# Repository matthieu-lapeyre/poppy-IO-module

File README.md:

poppy-IO-module
===============

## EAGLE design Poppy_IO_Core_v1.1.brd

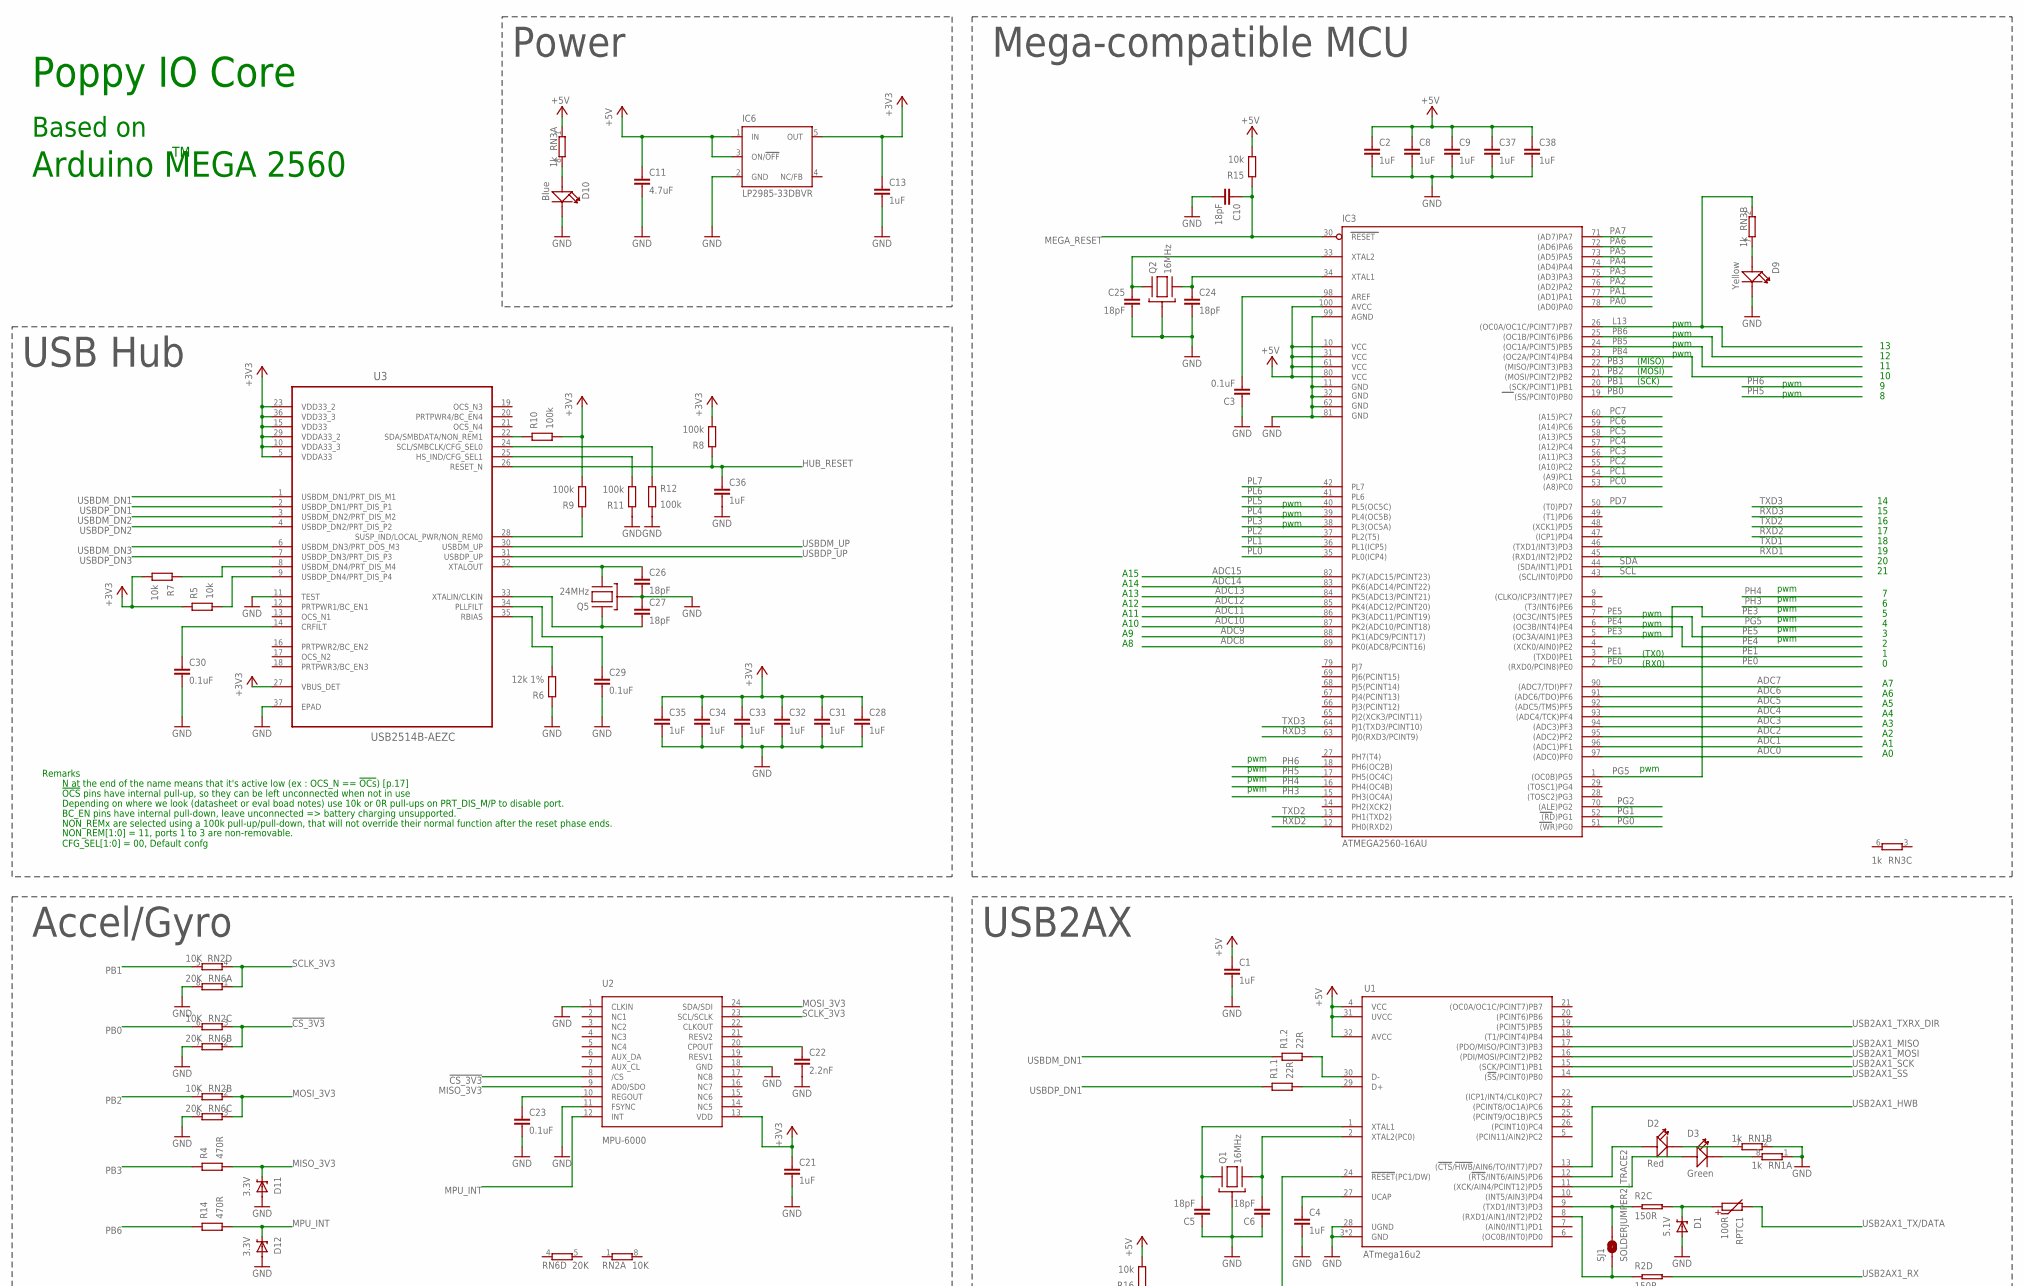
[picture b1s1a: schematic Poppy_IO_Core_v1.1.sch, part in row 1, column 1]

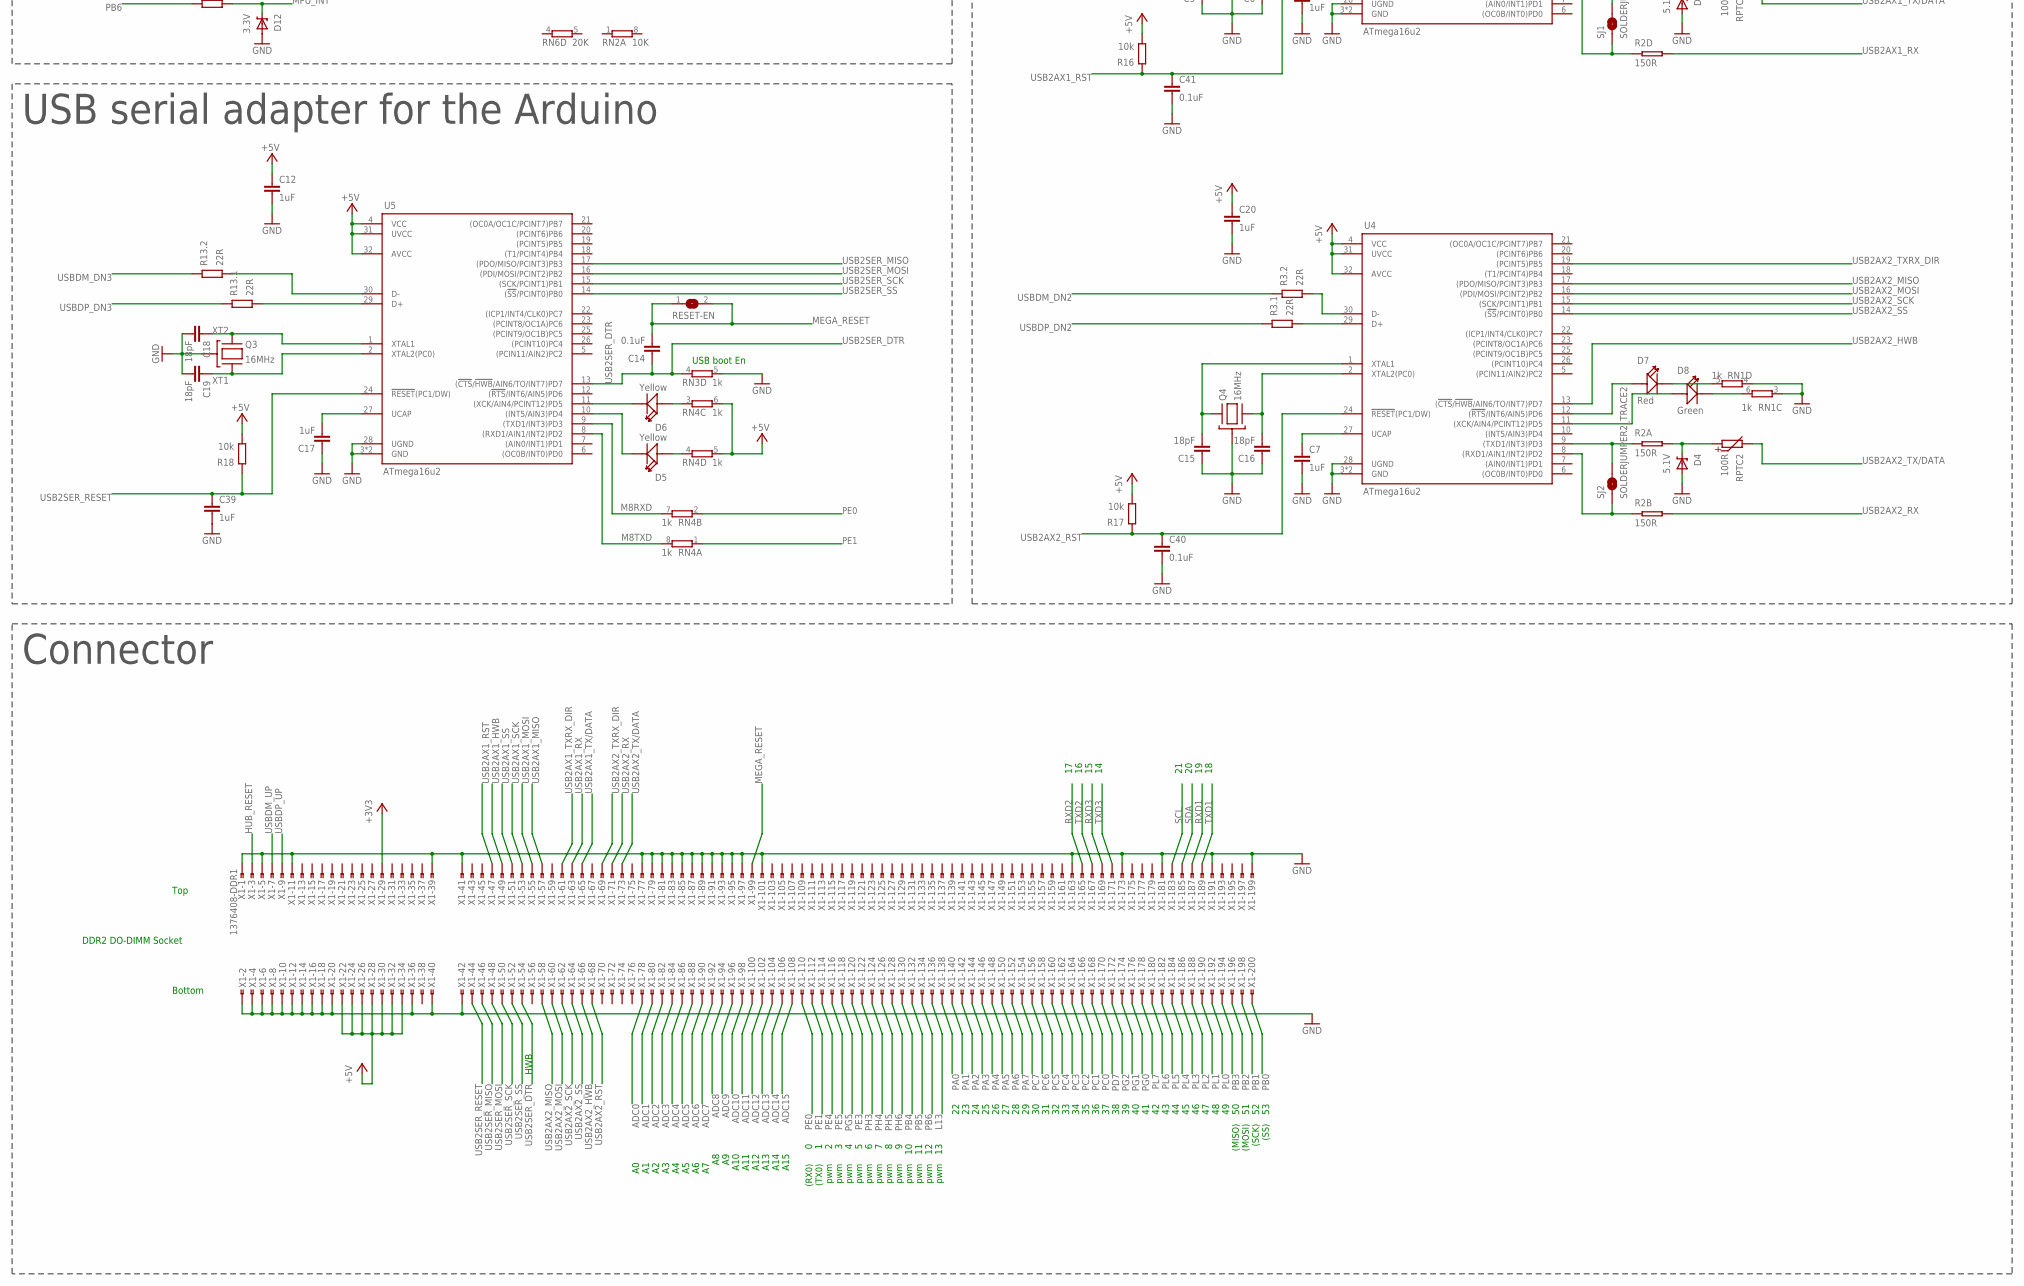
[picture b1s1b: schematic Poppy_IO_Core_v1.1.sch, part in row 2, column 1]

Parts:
C1, C2, C4, C7, C8, C9, C12, C13, C17, C20, C21, C28, C31, C32, C33, C34, C35, C36, C37, C38, C39: 1uF; 0402_N
C3, C14, C23, C29, C30, C40, C41: 0.1uF; 0402_N
C5, C6, C10, C15, C16, C18, C19, C24, C25, C26, C27: 18pF; 0402_N
C11: 4.7uF; 0805_N
C22: 2.2nF; 0402_N
D1, D4: 5.1V; SOD-923_N
D2, D7: Red; LED0603
D3, D8: Green; LED0603
D5, D6, D9: Yellow; LED0603
D10: Blue; LED0603
D11, D12: 3.3V; SOD-523_N
IC3: ATMEGA2560-16AU; TQFP100
IC6: LP2985-33DBVR; SOT23-DBV
Q1, Q2, Q3, Q4: 16MHz; CRYSTAL_MODEL-403_N
Q5: 24MHz; CRYSTAL_MODEL-403_N
R1, R3, R13: 22R; ARRAY_0402_65P_2_N
R2: 150R; R1206-8
R4, R14: 470R; 0402_N
R5, R7, R15, R16, R17, R18: 10k; 0402_N
R6: 12k 1%; 0402_N
R8, R9, R10, R11, R12: 100k; 0402_N
RESET-EN: SJ
RN1, RN3, RN4: 1k; CAY16
RN2: 10K; CAT16
RN6: 20K; CAT16
RPTC1, RPTC2: 100R; 0603_N
SJ1, SJ2: SOLDERJUMPER2_TRACE2; SJ_2S-TRACE2
U1, U4, U5: ATmega16u2; QFN-32_50P_N
U2: MPU-6000; QFN-24
U3: USB2514B-AEZC; QFN50P600X600X100-37N
X1: 1376408-DDR1; DDR1

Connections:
!CS_3V3: RN2.3 (1), RN6.2 (1), U2.8 (/CS)
+3V3: C13.1, C21.1, C28.1, C31.1, C32.1, C33.1, C34.1, C35.1, IC6.5 (OUT), R5.2, R7.1, R8.1, R9.1, R10.1, U2.13 (VDD), U3.5 (VDDA33), U3.10 (VDDA33_3), U3.15 (VDD33), U3.23 (VDD33_2), U3.27 (VBUS_DET), U3.29 (VDDA33_2), U3.36 (VDD33_3), X1.29
+5V: C1.1, C2.1, C8.1, C9.1, C11.1, C12.1, C20.1, C37.1, C38.1, IC3.10 (VCC), IC3.31 (VCC1), IC3.61 (VCC2), IC3.80 (VCC3), IC3.100 (AVCC), IC6.1 (IN), IC6.3 (ON/!OFF), R15.1, R16.1, R17.1, R18.1, RN3.1, RN4.5 (2), RN4.6 (2), U1.4 (VCC), U1.31 (UVCC), U1.32 (AVCC), U4.4 (VCC), U4.31 (UVCC), U4.32 (AVCC), U5.4 (VCC), U5.31 (UVCC), U5.32 (AVCC), X1.22, X1.24, X1.26, X1.28, X1.30, X1.32, X1.34
ADC0: IC3.97 ((ADC0)PF0), X1.78
ADC1: IC3.96 ((ADC1)PF1), X1.80
ADC2: IC3.95 ((ADC2)PF2), X1.82
ADC3: IC3.94 ((ADC3)PF3), X1.84
ADC4: IC3.93 ((ADC4/TCK)PF4), X1.86
ADC5: IC3.92 ((ADC5/TMS)PF5), X1.88
ADC6: IC3.91 ((ADC6/TDO)PF6), X1.90
ADC7: IC3.90 ((ADC7/TDI)PF7), X1.92
ADC8: IC3.89 (PK0(ADC8/PCINT16)), X1.94
ADC9: IC3.88 (PK1(ADC9/PCINT17)), X1.96
ADC10: IC3.87 (PK2(ADC10/PCINT18)), X1.98
ADC11: IC3.86 (PK3(ADC11/PCINT19)), X1.100
ADC12: IC3.85 (PK4(ADC12/PCINT20)), X1.102
ADC13: IC3.84 (PK5(ADC13/PCINT21)), X1.104
ADC14: IC3.83 (PK6(ADC14/PCINT22)), X1.106
ADC15: IC3.82 (PK7(ADC15/PCINT23)), X1.108
AREF: C3.2, IC3.98 (AREF)
GND: C1.2, C2.2, C3.1, C4.2, C5.1, C6.1, C7.2, C8.2, C9.2, C10.2, C11.2, C12.2, C13.2, C15.1, C16.1, C17.1, C18.2, C19.2, C20.2, C21.2, C22.2, C23.2, C24.2, C25.2, C26.2, C27.1, C28.2, C29.2, C30.2, C31.2, C32.2, C33.2, C34.2, C35.2, C36.2, C37.2, C38.2, C39.2, C40.2, C41.2, D1.A, D4.A, D9.-, D10.-, D11.A, D12.A, IC3.11 (GND), IC3.32 (GND1), IC3.62 (GND2), IC3.81 (GND3), IC3.99 (AGND), IC6.2 (GND), Q1.P$2 (GND), Q1.P$4 (GND), Q2.P$2 (GND), Q2.P$4 (GND), Q3.P$2 (GND), Q3.P$4 (GND), Q4.P$2 (GND), Q4.P$4 (GND), Q5.P$2 (GND), Q5.P$4 (GND), R6.2, R11.2, R12.1, RN1.1, RN1.2 (1), RN1.3 (1), RN1.4 (1), RN3.5 (2), RN6.6 (2), RN6.7 (2), RN6.8 (2), U1.3 (GND), U1.28 (UGND), U1.33 (GND), U2.1 (CLKIN), U2.11 (FSYNC), U2.18 (GND), U3.11 (TEST), U3.37 (EPAD), U4.3 (GND), U4.28 (UGND), U4.33 (GND), U5.3 (GND), U5.28 (UGND), U5.33 (GND), X1.1, X1.2, X1.4, X1.5, X1.6, X1.8, X1.10, X1.11, X1.12, X1.14, X1.16, X1.18, X1.20, X1.36, X1.39, X1.40, X1.41, X1.42, X1.77, X1.79, X1.81, X1.83, X1.85, X1.87, X1.89, X1.91, X1.93, X1.95, X1.97, X1.101, X1.163, X1.173, X1.181, X1.191, X1.199
HUB_RESET: C36.1, R8.2, U3.26 (RESET_N), X1.3
L13: IC3.26 ((OC0A/OC1C/PCINT7)PB7), RN3.2 (1), X1.136
M8RXD: RN4.7 (2), U5.9 ((TXD1/INT3)PD3)
M8TXD: RN4.8 (2), U5.8 ((RXD1/AIN1/INT2)PD2)
MEGA_RESET: C10.1, C14.2, IC3.30 (RESET), R15.2, RESET-EN.1, RESET-EN.2, X1.99
MISO_3V3: D11.C, R4.1, U2.9 (AD0/SDO)
MOSI_3V3: RN2.2 (1), RN6.3 (1), U2.24 (SDA/SDI)
MPU_INT: D12.C, R14.1, U2.12 (INT)
unnamed: D8.-, RN1.6 (2)
unnamed: R2.4 (1), SJ1.1, U1.8 ((RXD1/AIN1/INT2)PD2)
unnamed: C4.1, U1.27 (UCAP)
unnamed: D1.C, R2.6 (2), RPTC1.1
unnamed: D3.+, U1.11 ((XCK/AIN4/PCINT12)PD5)
unnamed: D10.+, RN3.8 (2)
unnamed: C6.2, Q1.P$3, U1.2 (XTAL2(PC0))
unnamed: C5.2, Q1.P$1, U1.1 (XTAL1)
unnamed: R1.1, U1.30 (D-)
unnamed: R1.2 (1), U1.29 (D+)
unnamed: D7.-, RN1.5 (2)
unnamed: D2.-, RN1.7 (2)
unnamed: D3.-, RN1.8 (2)
unnamed: R2.1, SJ2.2, U4.9 ((TXD1/INT3)PD3)
unnamed: D2.+, U1.12 ((!RTS!/INT6/AIN5)PD6)
unnamed: D9.+, RN3.7 (2)
unnamed: C7.1, U4.27 (UCAP)
unnamed: C16.2, Q4.P$3, U4.2 (XTAL2(PC0))
unnamed: C15.2, Q4.P$1, U4.1 (XTAL1)
unnamed: R2.3 (1), SJ1.2, U1.9 ((TXD1/INT3)PD3)
unnamed: R2.2 (1), SJ2.1, U4.8 ((RXD1/AIN1/INT2)PD2)
unnamed: D4.C, R2.8 (2), RPTC2.1
unnamed: R3.1, U4.30 (D-)
unnamed: R3.2 (1), U4.29 (D+)
unnamed: D8.+, U4.11 ((XCK/AIN4/PCINT12)PD5)
unnamed: D7.+, U4.12 ((!RTS!/INT6/AIN5)PD6)
unnamed: C23.1, U2.10 (REGOUT)
unnamed: C26.1, Q5.P$3, U3.32 (XTALOUT)
unnamed: C22.1, U2.20 (CPOUT)
unnamed: R7.2, U3.8 (USBDM_DN4/PRT_DIS_M4)
unnamed: C27.2, Q5.P$1, U3.33 (XTALIN/CLKIN)
unnamed: R5.1, U3.9 (USBDP_DN4/PRT_DIS_P4)
unnamed: C30.1, U3.14 (CRFILT)
unnamed: R9.2, U3.28 (SUSP_IND/LOCAL_PWR/NON_REM0)
unnamed: C29.1, U3.34 (PLLFILT)
unnamed: R6.1, U3.35 (RBIAS)
unnamed: R10.2, U3.22 (SDA/SMBDATA/NON_REM1)
unnamed: R12.2, U3.24 (SCL/SMBCLK/CFG_SEL0)
unnamed: R11.1, U3.25 (HS_IND/CFG_SEL1)
unnamed: D5.+, RN4.4 (1)
unnamed: D6.+, RN4.3 (1)
PA0: IC3.78 ((AD0)PA0), X1.138
PA1: IC3.77 ((AD1)PA1), X1.140
PA2: IC3.76 ((AD2)PA2), X1.142
PA3: IC3.75 ((AD3)PA3), X1.144
PA4: IC3.74 ((AD4)PA4), X1.146
PA5: IC3.73 ((AD5)PA5), X1.148
PA6: IC3.72 ((AD6)PA6), X1.150
PA7: IC3.71 ((AD7)PA7), X1.152
PB0: IC3.19 ((SS/PCINT0)PB0), RN2.6 (2), X1.200
PB1: IC3.20 ((SCK/PCINT1)PB1), RN2.5 (2), X1.198
PB2: IC3.21 ((MOSI/PCINT2)PB2), RN2.7 (2), X1.196
PB3: IC3.22 ((MISO/PCINT3)PB3), R4.2, X1.194
PB4: IC3.23 ((OC2A/PCINT4)PB4), X1.130
PB5: IC3.24 ((OC1A/PCINT5)PB5), X1.132
PB6: IC3.25 ((OC1B/PCINT6)PB6), R14.2, X1.134
PC0: IC3.53 ((A8)PC0), X1.168
PC1: IC3.54 ((A9)PC1), X1.166
PC2: IC3.55 ((A10)PC2), X1.164
PC3: IC3.56 ((A11)PC3), X1.162
PC4: IC3.57 ((A12)PC4), X1.160
PC5: IC3.58 ((A13)PC5), X1.158
PC6: IC3.59 ((A14)PC6), X1.156
PC7: IC3.60 ((A15)PC7), X1.154
PD7: IC3.50 ((T0)PD7), X1.170
PE0: IC3.2 ((RXD0/PCIN8)PE0), RN4.2 (1), X1.110
PE1: IC3.3 ((TXD0)PE1), RN4.1, X1.112
PE3: IC3.5 ((OC3A/AIN1)PE3), X1.120
PE4: IC3.6 ((OC3B/INT4)PE4), X1.114
PE5: IC3.7 ((OC3C/INT5)PE5), X1.116
PG0: IC3.51 ((WR)PG0), X1.176
PG1: IC3.52 ((RD)PG1), X1.174
PG2: IC3.70 ((ALE)PG2), X1.172
PG5: IC3.1 ((OC0B)PG5), X1.118
PH3: IC3.15 (PH3(OC4A)), X1.122
PH4: IC3.16 (PH4(OC4B)), X1.124
PH5: IC3.17 (PH5(OC4C)), X1.126
PH6: IC3.18 (PH6(OC2B)), X1.128
PL0: IC3.35 (PL0(ICP4)), X1.192
PL1: IC3.36 (PL1(ICP5)), X1.190
PL2: IC3.37 (PL2(T5)), X1.188
PL3: IC3.38 (PL3(OC5A)), X1.186
PL4: IC3.39 (PL4(OC5B)), X1.184
PL5: IC3.40 (PL5(OC5C)), X1.182
PL6: IC3.41 (PL6), X1.180
PL7: IC3.42 (PL7), X1.178
RD+: R13.2 (1), U5.29 (D+)
RD-: R13.1, U5.30 (D-)
RXD1: IC3.45 ((RXD1/INT2)PD2), X1.187
RXD2: IC3.12 (PH0(RXD2)), X1.165
RXD3: IC3.63 (PJ0(RXD3/PCINT9)), X1.169
RXL: D5.-, U5.10 ((INT5/AIN3)PD4)
SCL: IC3.43 ((SCL/INT0)PD0), X1.183
SCLK_3V3: RN2.4 (1), RN6.1, U2.23 (SCL/SCLK)
SDA: IC3.44 ((SDA/INT1)PD1), X1.185
TXD1: IC3.46 ((TXD1/INT3)PD3), X1.189
TXD2: IC3.13 (PH1(TXD2)), X1.167
TXD3: IC3.64 (PJ1(TXD3/PCINT10)), X1.171
TXL: D6.-, U5.11 ((XCK/AIN4/PCINT12)PD5)
USB2AX1_HWB: U1.13 ((!CTS!/!HWB!/AIN6/TO/INT7)PD7), X1.49
USB2AX1_MISO: U1.17 ((PDO/MISO/PCINT3)PB3), X1.57
USB2AX1_MOSI: U1.16 ((PDI/MOSI/PCINT2)PB2), X1.55
USB2AX1_RST: C41.1, R16.2, U1.24 (!RESET!(PC1/DW)), X1.47
USB2AX1_RX: R2.5 (2), X1.63
USB2AX1_SCK: U1.15 ((SCK/PCINT1)PB1), X1.53
USB2AX1_SS: U1.14 ((!SS!/PCINT0)PB0), X1.51
USB2AX1_TX/DATA: RPTC1.2, X1.65
USB2AX1_TXRX_DIR: U1.19 ((PCINT5)PB5), X1.61
USB2AX2_HWB: U4.13 ((!CTS!/!HWB!/AIN6/TO/INT7)PD7), X1.66
USB2AX2_MISO: U4.17 ((PDO/MISO/PCINT3)PB3), X1.58
USB2AX2_MOSI: U4.16 ((PDI/MOSI/PCINT2)PB2), X1.60
USB2AX2_RST: C40.1, R17.2, U4.24 (!RESET!(PC1/DW)), X1.68
USB2AX2_RX: R2.7 (2), X1.71
USB2AX2_SCK: U4.15 ((SCK/PCINT1)PB1), X1.62
USB2AX2_SS: U4.14 ((!SS!/PCINT0)PB0), X1.64
USB2AX2_TX/DATA: RPTC2.2, X1.73
USB2AX2_TXRX_DIR: U4.19 ((PCINT5)PB5), X1.69
USB2SER_DTR: C14.1, RN3.4 (1), U5.13 ((!CTS!/!HWB!/AIN6/TO/INT7)PD7), X1.54
USB2SER_MISO: U5.17 ((PDO/MISO/PCINT3)PB3), X1.46
USB2SER_MOSI: U5.16 ((PDI/MOSI/PCINT2)PB2), X1.48
USB2SER_RESET: C39.1, R18.2, U5.24 (!RESET!(PC1/DW)), X1.44
USB2SER_SCK: U5.15 ((SCK/PCINT1)PB1), X1.50
USB2SER_SS: U5.14 ((!SS!/PCINT0)PB0), X1.52
USBDM_DN1: R1.4 (2), U3.1 (USBDM_DN1/PRT_DIS_M1)
USBDM_DN2: R3.4 (2), U3.3 (USBDM_DN2/PRT_DIS_M2)
USBDM_DN3: R13.4 (2), U3.6 (USBDM_DN3/PRT_DOS_M3)
USBDM_UP: U3.30 (USBDM_UP), X1.7
USBDP_DN1: R1.3 (2), U3.2 (USBDP_DN1/PRT_DIS_P1)
USBDP_DN2: R3.3 (2), U3.4 (USBDP_DN2/PRT_DIS_P2)
USBDP_DN3: R13.3 (2), U3.7 (USBDP_DN3/PRT_DIS_P3)
USBDP_UP: U3.31 (USBDP_UP), X1.9
VUCAP: C17.2, U5.27 (UCAP)
XT1: C19.1, Q3.P$3, U5.2 (XTAL2(PC0))
XT2: C18.1, Q3.P$1, U5.1 (XTAL1)
XTAL1: C24.1, IC3.34 (XTAL1), Q2.P$3
XTAL2: C25.1, IC3.33 (XTAL2), Q2.P$1

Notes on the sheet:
Top
Bottom
DDR2 DO-DIMM Socket
Arduino MEGA 2560
pwm
(TX0)
(RX0)
(MISO)
(SCK)
(MOSI)
(SS)
USB boot En
Based on
Accel/Gyro
Depending on where we look (datasheet or eval boad notes) use 10k or 0R pull-ups on PRT_DIS_M/P to disable port.
NON_REM[1:0] = 11, ports 1 to 3 are non-removable. CFG_SEL[1:0] = 00, Default confg
!OCS! pins have internal pull-up, so they can be left unconnected when not in use
N at the end of the name means that it's active low (ex : OCS_N == !OCs!) [p.17]
Remarks
BC_EN pins have internal pull-down, leave unconnected => battery charging unsupported.
NON_REMx are selected using a 100k pull-up/pull-down, that will not override their normal function after the reset phase ends.
USB Hub
USB2AX
Power
Connector
USB serial adapter for the Arduino
Poppy IO Core
A10
A11
A12
A13
A14
A15
Mega-compatible MCU
HWB

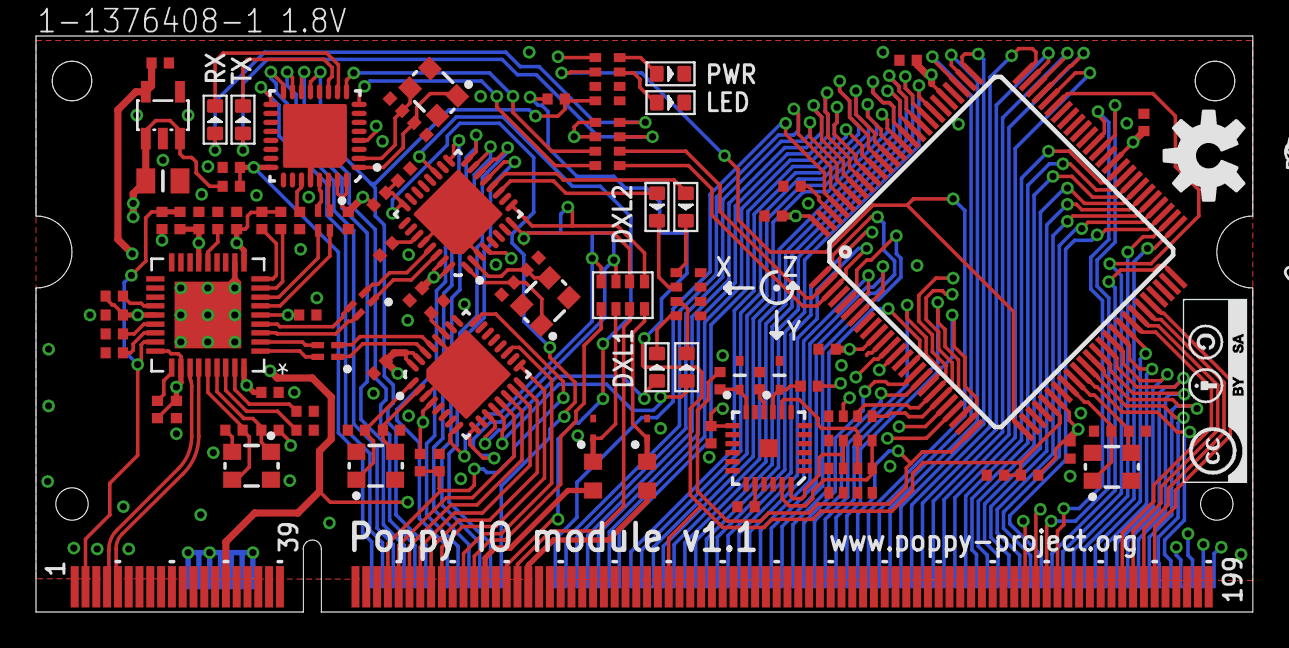
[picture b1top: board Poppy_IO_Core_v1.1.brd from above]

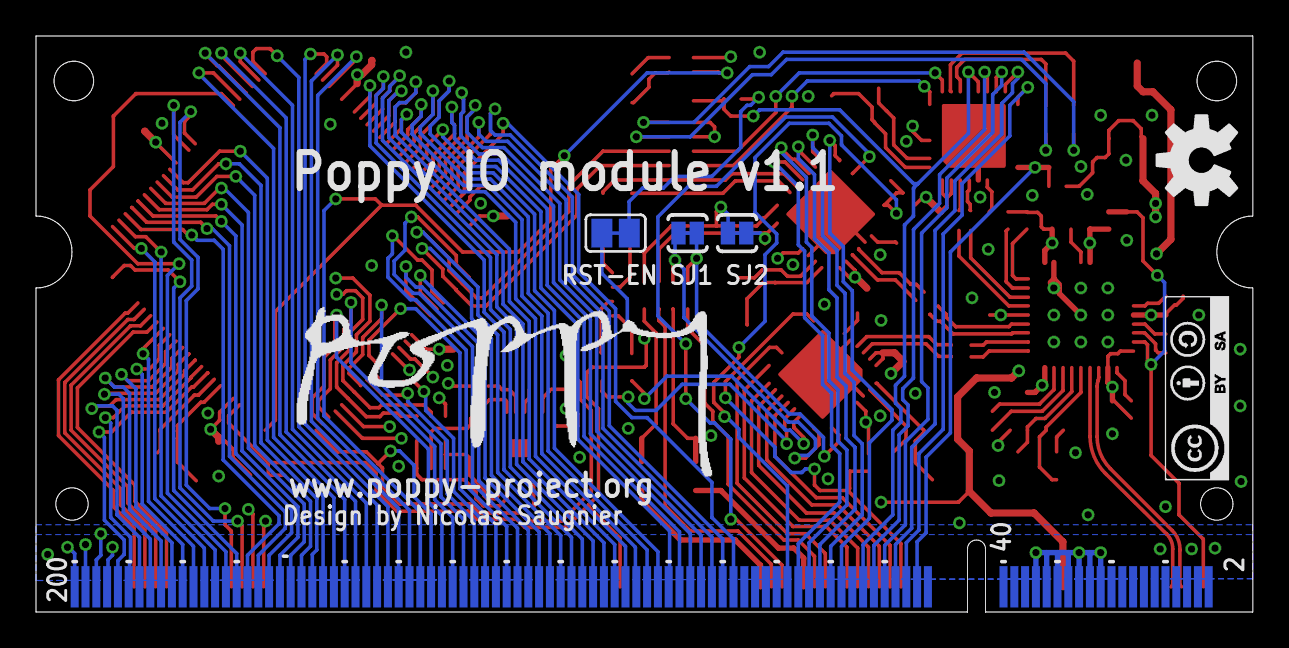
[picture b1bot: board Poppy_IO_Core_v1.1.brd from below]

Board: 4 copper layers, 67.6 x 32.0 mm, 98 parts (5 on the bottom side), 165 nets.

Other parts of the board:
U$1, U$3: OSHW-LOGO-M
U$2, U$4: CC-BY-SA

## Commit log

2014-08-29 Added initial files. Schematics and routing are done, cosmetic changes are still needed.
2014-08-29 Connected some (important) signals that had been omitted.
2014-08-29 Aesthetics of the board done (text / logos)
2014-08-30 Replaced 3.3V SOD-923 LEDs with ones easier to source.
2014-08-31 Corrected a problem with paste layer (paste on the gold contacts would have made for a poor result...).
2014-08-31 Adjusted visible layers
2014-09-11 Some cosmetic adjustment so that it looks as supposed in circuithub: - removed names and values from the board to hide them (no way to hide the layer!) - removed all solder paste on the back
2015-09-27 Addede v1.1 : changed footprint to DDR1
2015-11-19 remove old version

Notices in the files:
parts and their libraries:
SparkFun-Aesthetics: Licensing: CC v3.0 Share-Alike You are welcome to use this library for commercial purposes.
